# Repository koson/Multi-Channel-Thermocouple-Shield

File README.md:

# Multi-Channel-Thermocouple-Shield
Multi Channel Thermocouple Shield MAX6675

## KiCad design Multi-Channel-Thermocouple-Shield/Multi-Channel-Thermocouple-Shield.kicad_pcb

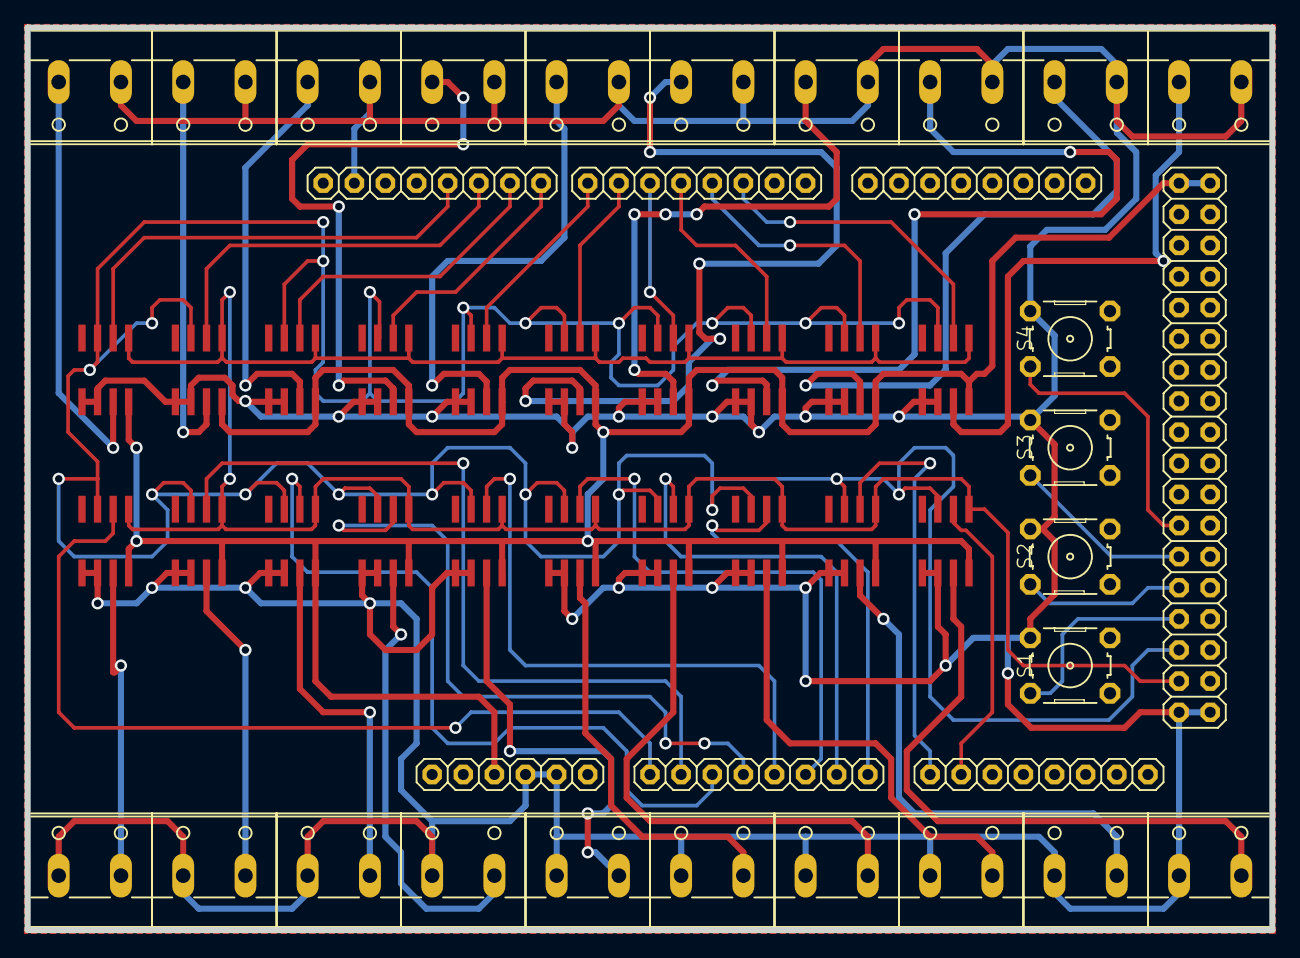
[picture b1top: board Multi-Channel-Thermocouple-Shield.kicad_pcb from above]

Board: 2 copper layers, 101.6 x 73.7 mm, 45 parts (0 on the bottom side), 48 nets.

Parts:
IC1: MEGA_ARDUINO
S1, S2, S3, S4: B3F-10XX
U$1, U$2, U$3, U$4, U$5, U$6, U$7, U$8, U$9, U$10, U$11, U$12, U$13, U$14, U$15, U$16, U$17, U$18, U$19, U$20: MAX6675; SO08
X1, X2, X3, X4, X5, X6, X7, X8, X9, X10, X11, X12, X13, X14, X15, X16, X17, X18, X19, X20: W237-132

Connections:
CS0: IC1.16, U$1.6
CS1: IC1.15, U$2.6
CS2: IC1.14, U$3.6
CS3: IC1.13, U$4.6
CS4: IC1.12, U$5.6
CS5: IC1.11, U$6.6
CS6: IC1.10, U$7.6
CS7: IC1.9, U$8.6
CS8: IC1.8, U$9.6
CS9: IC1.7, U$10.6
CS10: IC1.33, U$11.6
CS11: IC1.34, U$12.6
CS12: IC1.35, U$13.6
CS13: IC1.36, U$14.6
CS14: IC1.37, U$15.6
CS15: IC1.38, U$16.6
CS16: IC1.39, U$17.6
CS17: IC1.40, U$18.6
CS18: IC1.41, U$19.6
CS19: IC1.42, U$20.6
GND: IC1.4, IC1.5, IC1.45, IC1.81, IC1.82, S1.1, S2.1, S3.1, S4.1, U$1.1, U$1.2, U$2.1, U$2.2, U$3.1, U$3.2, U$4.1, U$4.2, U$5.1, U$5.2, U$6.1, U$6.2, U$7.1, U$7.2, U$8.1, U$8.2, U$9.1, U$9.2, U$10.1, U$10.2, U$11.1, U$11.2, U$12.1, U$12.2, U$13.1, U$13.2, U$14.1, U$14.2, U$15.1, U$15.2, U$16.1, U$16.2, U$17.1, U$17.2, U$18.1, U$18.2, U$19.1, U$19.2, U$20.1, U$20.2, X1.1, X2.1, X3.1, X4.1, X5.1, X6.1, X7.1, X8.1, X9.1, X10.1, X11.1, X12.1, X13.1, X14.1, X15.1, X16.1, X17.1, X18.1, X19.1, X20.1
MISO: IC1.77, U$1.7, U$2.7, U$3.7, U$4.7, U$5.7, U$6.7, U$7.7, U$8.7, U$9.7, U$10.7, U$11.7, U$12.7, U$13.7, U$14.7, U$15.7, U$16.7, U$17.7, U$18.7, U$19.7, U$20.7
unnamed: U$10.3, X10.2
unnamed: U$1.3, X1.2
unnamed: U$2.3, X2.2
unnamed: U$3.3, X3.2
unnamed: U$4.3, X4.2
unnamed: U$5.3, X5.2
unnamed: U$6.3, X6.2
unnamed: U$7.3, X7.2
unnamed: U$8.3, X8.2
unnamed: U$9.3, X9.2
unnamed: U$11.3, X11.2
unnamed: U$12.3, X12.2
unnamed: U$13.3, X13.2
unnamed: U$14.3, X14.2
unnamed: U$15.3, X15.2
unnamed: U$16.3, X16.2
unnamed: U$17.3, X17.2
unnamed: U$18.3, X18.2
unnamed: U$19.3, X19.2
unnamed: U$20.3, X20.2
SCK: IC1.79, U$1.5, U$2.5, U$3.5, U$4.5, U$5.5, U$6.5, U$7.5, U$8.5, U$9.5, U$10.5, U$11.5, U$12.5, U$13.5, U$14.5, U$15.5, U$16.5, U$17.5, U$18.5, U$19.5, U$20.5
SW1: IC1.75, S1.3
SW2: IC1.73, S2.3
SW3: IC1.71, S3.3
SW4: IC1.69, S4.3
VCC: IC1.3, IC1.47, IC1.48, U$1.4, U$2.4, U$3.4, U$4.4, U$5.4, U$6.4, U$7.4, U$8.4, U$9.4, U$10.4, U$11.4, U$12.4, U$13.4, U$14.4, U$15.4, U$16.4, U$17.4, U$18.4, U$19.4, U$20.4

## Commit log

2017-10-03 Added HW Design Files
2023-02-24 add kicad
2024-04-09 kicad
